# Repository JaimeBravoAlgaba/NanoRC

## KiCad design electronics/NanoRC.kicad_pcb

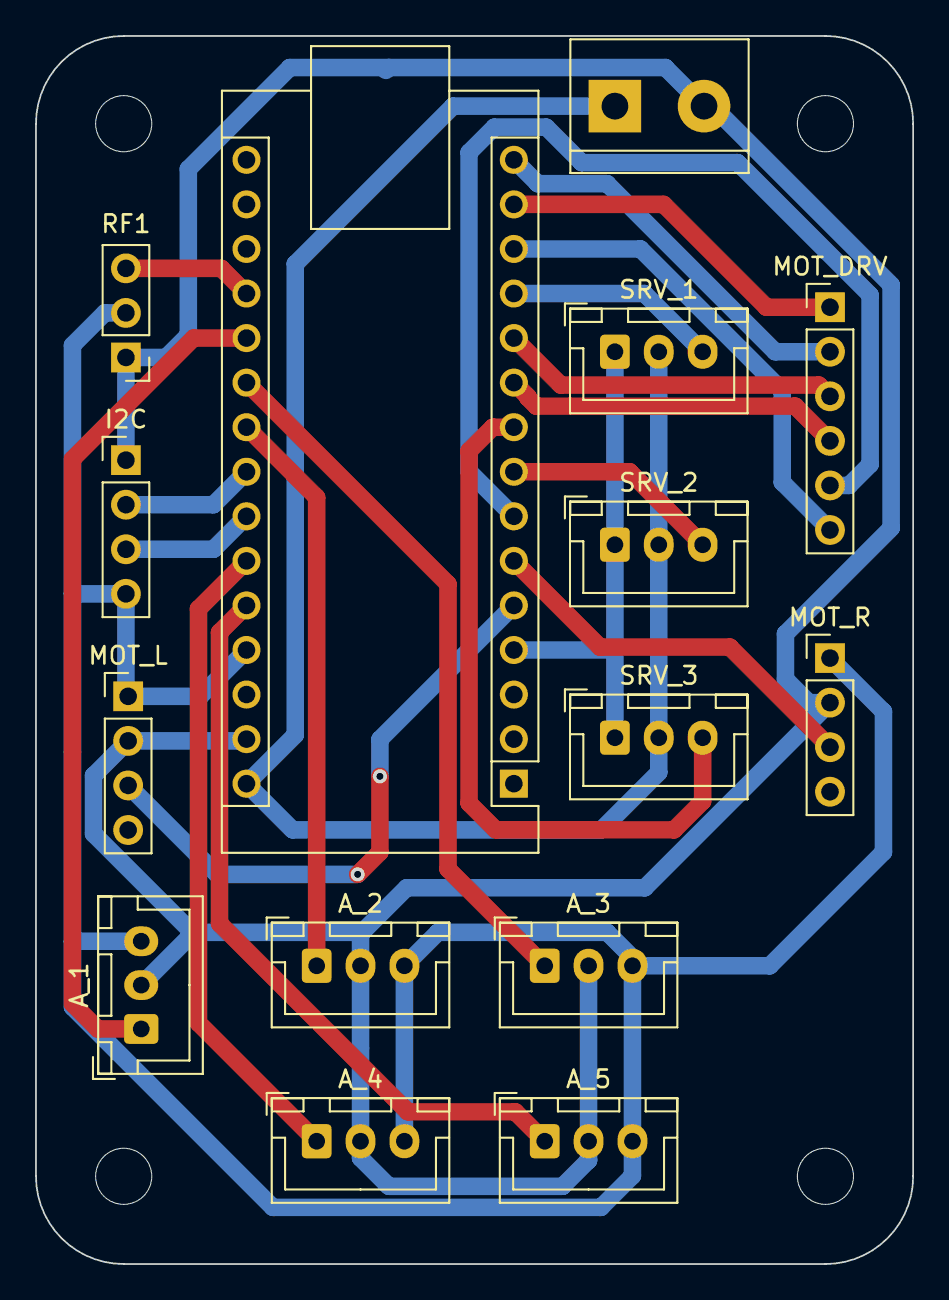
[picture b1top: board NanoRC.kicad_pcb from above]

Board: 2 copper layers, 50.0 x 70.0 mm, 19 parts (0 on the bottom side), 22 nets.

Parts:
A1: Arduino_Nano_Every; Arduino_Nano
A_1, A_2, A_3, A_4, A_5: Conn_01x03; JST_XH_B3B-XH-A_1x03_P2.50mm_Vertical
H1, H2, H3, H4: MountingHole; MountingHole_3.2mm_M3
I2C: Conn_01x04_Pin; PinHeader_1x04_P2.54mm_Vertical
MOT_DRV: Conn_01x06_Pin; PinHeader_1x06_P2.54mm_Vertical
MOT_L: Conn_01x04_Pin; PinHeader_1x04_P2.54mm_Vertical
MOT_R: Conn_01x04_Pin; PinHeader_1x04_P2.54mm_Vertical
PWR: Conn_01x02_Pin; TerminalBlock_bornier-2_P5.08mm
RF1: Conn_01x03; PinHeader_1x03_P2.54mm_Vertical
SRV_1, SRV_2, SRV_3: Conn_01x03; JST_XH_B3B-XH-A_1x03_P2.50mm_Vertical

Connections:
+5V: A1.27 (+5V), A_1.3, A_2.3, A_3.3, A_4.3, A_5.3, I2C.4, MOT_L.1, MOT_R.1, RF1.2
A_0: A1.20 (A1), A_1.1
A_1: A1.22 (A3), A_2.1
A_2: A1.21 (A2), A_3.1
A_3: A1.25 (A6), A_4.1
A_4: A1.26 (A7), A_5.1
ENC_L: A1.5 (D2), MOT_L.3
ENC_R: A1.6 (D3), MOT_R.3
GND: A1.4 (GND), A1.29 (GND), A_1.2, A_2.2, A_3.2, A_4.2, A_5.2, I2C.1, MOT_L.2, MOT_R.2, PWR.2, RF1.1, SRV_1.1, SRV_2.1, SRV_3.1
INA_L: A1.15 (MISO), MOT_DRV.2
INA_R: A1.10 (D7), MOT_DRV.4
INB_L: A1.11 (D8), MOT_DRV.3
INB_R: A1.7 (D4), MOT_DRV.5
PPM: A1.19 (A0), RF1.3
PWM_0: A1.12 (D9), SRV_1.3
PWM_1: A1.8 (D5), SRV_2.3
PWM_2: A1.9 (D6), SRV_3.3
PWM_L: A1.14 (MOSI), MOT_DRV.1
PWM_R: A1.13 (D10), MOT_DRV.6
SCL: A1.24 (SCL/A5), I2C.3
SDA: A1.23 (SDA/A4), I2C.2
VDC: A1.30 (VIN), PWR.1, SRV_1.2, SRV_2.2, SRV_3.2

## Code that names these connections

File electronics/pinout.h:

#pragma once
	#define PPM A0
	#define A_0 A1
	#define A_2 A2
	#define A_1 A3
	#define SDA A4
	#define SCL A5
	#define A_3 A6
	#define A_4 A7	
	#define ENC_L 2
	#define ENC_R 3
	#define INB_R 4
	#define PWM_1 5
	#define PWM_2 6
	#define INA_R 7
	#define INB_L 8
	#define PWM_0 9
	#define PWM_R 10
	#define PWM_L 11
	#define INA_L 12

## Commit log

2023-04-11 Primera versión
